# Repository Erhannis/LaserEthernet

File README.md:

Warning: I did not get it working, though I only spent like half an hour trying before I got distracted with something else.

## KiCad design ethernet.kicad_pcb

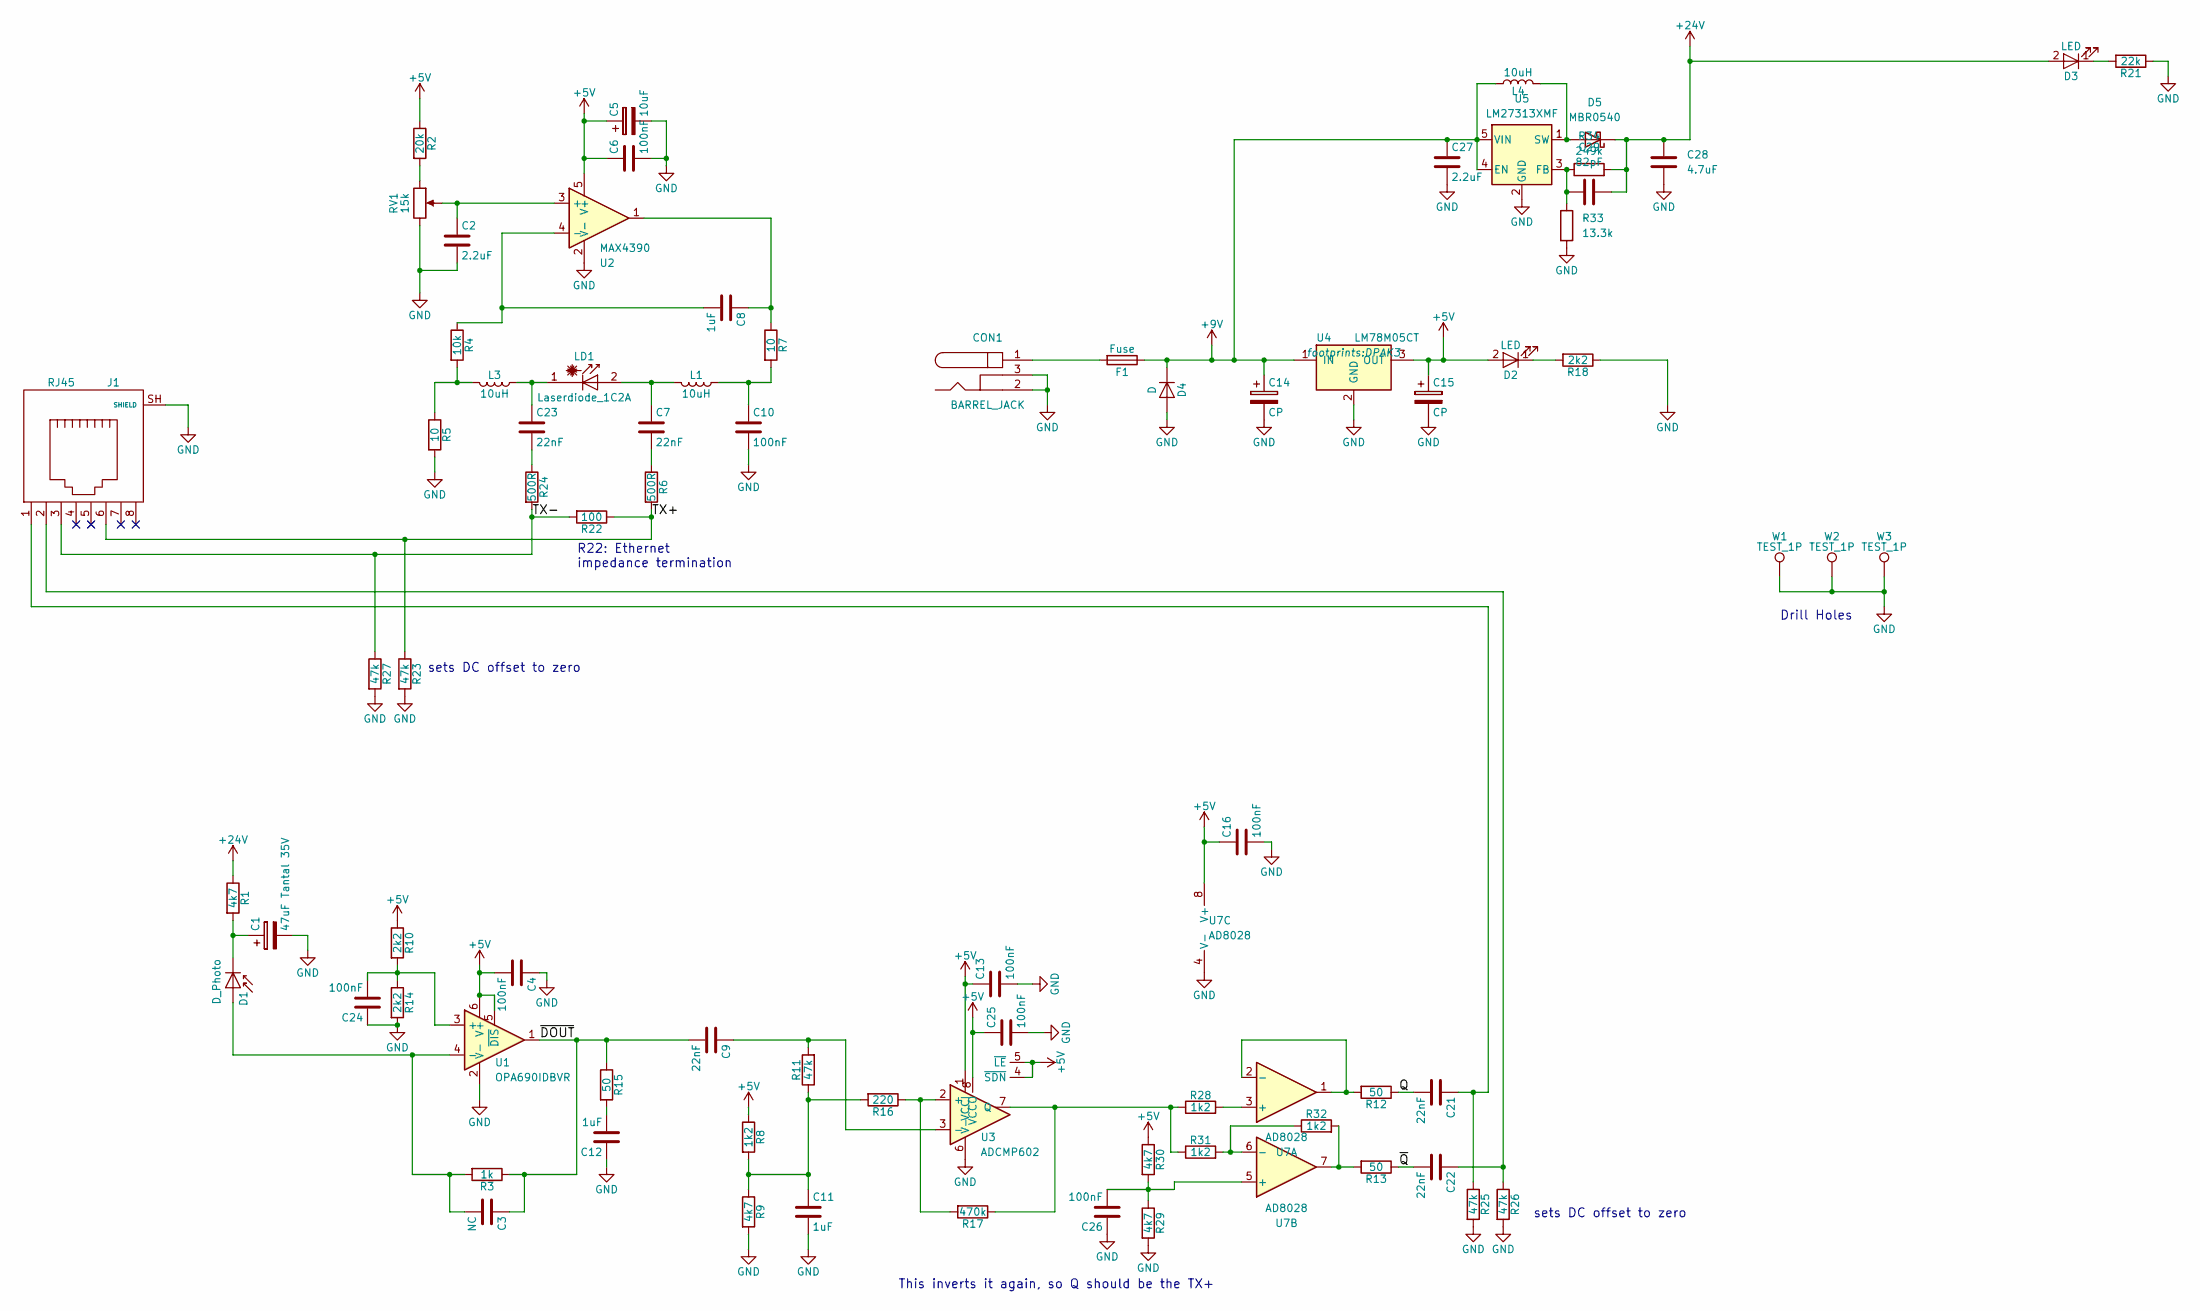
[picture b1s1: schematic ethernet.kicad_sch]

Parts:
C1: 47uF Tantal 35V; CP_Tantalum_Case-V_EIA-7343-20_Reflow; LCSC C600570
C2: 2.2uF; C_0603_HandSoldering; LCSC C913904
C3: NC; C_0603_HandSoldering
C4, C6, C10, C13, C24: 100nF; C_0603_HandSoldering; LCSC C30926
C5: 10uF; CP_Elec_4x5.8; LCSC C401709
C7, C9, C21, C22, C23: 22nF; C_0603_HandSoldering; LCSC C77571
C8, C11, C12: 1uF; C_0603_HandSoldering; LCSC C15849
C14, C15: CP; CP_Elec_4x5.8; LCSC C401709
C16, C25, C26: 100nF; C_0603_1608Metric_Pad1.08x0.95mm_HandSolder; LCSC C30926
C27: 2.2uF; C_0603_1608Metric; LCSC C913904
C28: 4.7uF; C_0603_1608Metric; LCSC C162274
C29: 82pF; C_0402_1005Metric; LCSC C526982
CON1: BARREL_JACK; LCSC C431533
D1: D_Photo; LED_D3.0mm_Horicontal_O2.54mm; LCSC C145493
D2: LED; D_0603_1608Metric; LCSC C72043
D3: LED; D_0603_1608Metric; LCSC C965808
D4: D; D_0603_1608Metric; LCSC C143772
D5: MBR0540; D_SOD-123
F1: Fuse; Fuseholder5x20_horiz_SemiClosed_Casing10x25mm; LCSC C58066
J1: RJ45; RJ45_Ninigi_GE; LCSC C3001538
L1, L3, L4: 10uH; L_1210_3225Metric; LCSC C250231
LD1: Laserdiode_1C2A; laserdiode_6mm
R1, R9: 4k7; R_0603_HandSoldering; LCSC C23162
R2: 20k; R_0603_HandSoldering; LCSC C4184
R3: 1k; R_0603_HandSoldering; LCSC C21190
R4: 10k; R_0603_HandSoldering; LCSC C25804
R5, R7: 10; R_0603_HandSoldering; LCSC C22859
R6, R24: 500R; R_0603_HandSoldering; LCSC C23065
R8: 1k2; R_0603_HandSoldering; LCSC C22765
R10, R14, R18: 2k2; R_0603_HandSoldering; LCSC C4190
R11, R23, R25, R26, R27: 47k; R_0603_HandSoldering; LCSC C25819
R12, R13, R15: 50; R_0603_HandSoldering; LCSC C23185
R16: 220; R_0603_HandSoldering; LCSC C22962
R17: 470k; R_0603_HandSoldering; LCSC C23178
R21: 22k; R_0603_HandSoldering; LCSC C31850
R22: 100; R_0603_HandSoldering; LCSC C22775
R28, R31, R32: 1k2; R_0603_1608Metric_Pad0.98x0.95mm_HandSolder; LCSC C22765
R29, R30: 4k7; R_0603_1608Metric_Pad0.98x0.95mm_HandSolder; LCSC C23162
R33: 13.3k; R_0402_1005Metric; LCSC C274352
R34: 249k; R_0402_1005Metric; LCSC C409682
RV1: 15k; TC33k; LCSC C128550
U1: OPA690IDBVR; SOT-23-6; LCSC C524799
U2: MAX4390; SOT-23-5; LCSC C652243
U3: ADCMP602; MSOP-8_3x3mm_P0.65mm; LCSC C207991
U4: LM78M05CT; DPAK3; LCSC C9070
U5: LM27313XMF; SOT-23-5
U7: AD8028; SOIC-8_3.9x4.9mm_P1.27mm; LCSC C652202
W1, W2, W3: TEST_1P; 3mm_drill

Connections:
+5V: C4.2, C5.1, C6.1, C13.1, C15.1, C16.1, C25.1, D2.2 (A), R2.1, R8.1, R10.1, R30.1, U1.5 (~DIS), U1.6 (V+), U2.5 (V+), U3.1 (VCCI), U3.4 (~SDN), U3.5 (~LE), U3.8 (VCCO), U4.3 (OUT), U7.8 (V+)
+9V: C14.1, C27.1, D4.1 (K), F1.1, L4.1, U4.1 (IN), U5.4 (EN), U5.5 (VIN)
+24V: C28.1, C29.2, D3.2 (A), D5.1 (K), R1.1, R34.2
/Q: C21.2, R12.1
/TX+: J1.6, R6.2, R22.1, R23.1
/TX-: J1.3, R22.2, R24.2, R27.1
/~DOUT: C3.1, C9.2, R3.1, R15.1, U1.1
/~Q: C22.2, R13.1
GND: C1.2, C2.2, C4.1, C5.2, C6.2, C10.2, C11.2, C12.1, C13.2, C14.2, C15.2, C16.2, C24.1, C25.2, C26.1, C27.2, C28.2, CON1.2, CON1.3, D4.2 (A), J1.SH (SHIELD), R5.2, R9.2, R14.2, R18.1, R21.1, R23.2, R25.2, R26.2, R27.2, R29.2, R33.2, RV1.3, U1.2 (V-), U2.2 (V-), U3.6 (V-), U4.2 (GND), U5.2 (GND), U7.4 (V-), W1.1, W2.1, W3.1
unnamed: C7.2, R6.1
unnamed: C8.1, R7.1, U2.1
unnamed: C10.1, L1.1, R7.2
unnamed: C11.1, R8.2, R9.1, R11.1, R16.2
unnamed: C12.2, R15.2
unnamed: C21.1, J1.1, R25.1
unnamed: C22.1, J1.2, R26.1
unnamed: C23.2, R24.1
unnamed: CON1.1, F1.2
unnamed: C3.2, D1.2 (A), R3.2, U1.4 (-)
unnamed: C1.1, D1.1 (K), R1.2
unnamed: D2.1 (K), R18.2
unnamed: D3.1 (K), R21.2
unnamed: D5.2 (A), L4.2, U5.1 (SW)
unnamed: L3.2, R4.2, R5.1
unnamed: C7.1, L1.2, LD1.2 (A)
unnamed: C23.1, L3.1, LD1.1 (K)
unnamed: R2.2, RV1.1
unnamed: R13.2, R32.2, U7.7
unnamed: C24.2, R10.2, R14.1, U1.3 (+)
unnamed: C2.1, RV1.2, U2.3 (+)
unnamed: C8.2, R4.1, U2.4 (-)
unnamed: R16.1, R17.2, U3.2 (+)
unnamed: C9.1, R11.2, U3.3 (-)
unnamed: R17.1, R28.1, R31.1, U3.7 (Q)
unnamed: C29.1, R33.1, R34.1, U5.3 (FB)
unnamed: R28.2, U7.3 (+)
unnamed: R12.2, U7.1, U7.2 (-)
unnamed: C26.2, R29.1, R30.2, U7.5 (+)
unnamed: R31.2, R32.1, U7.6 (-)

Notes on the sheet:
R22: Ethernet impedance termination
sets DC offset to zero
Drill Holes
This inverts it again, so Q should be the TX+

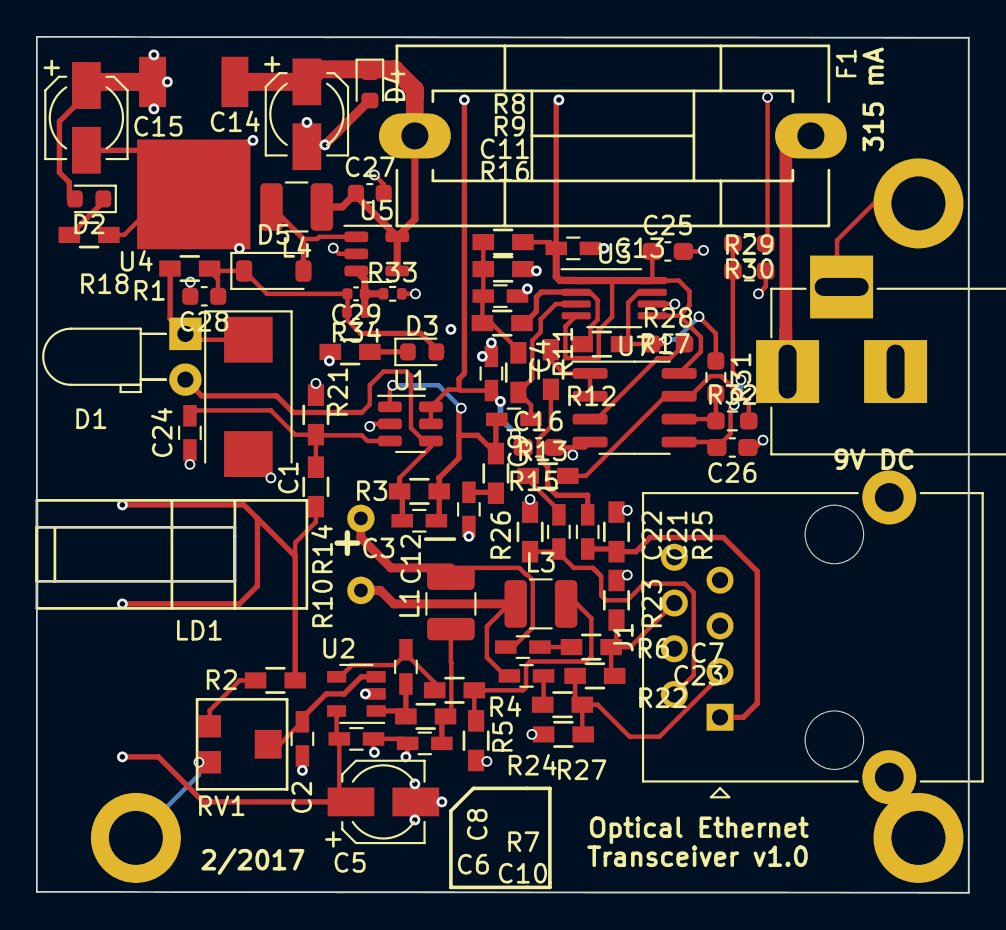
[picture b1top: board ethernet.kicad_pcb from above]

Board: 2 copper layers, 51.8 x 47.5 mm, 79 parts (0 on the bottom side), 39 nets.

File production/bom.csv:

Designator,Footprint,Quantity,Value,LCSC Part #
C1,CP_Tantalum_Case-V_EIA-7343-20_Reflow,1,47uF Tantal 35V,C600570
"C10, C13, C24, C4, C6",C_0603_HandSoldering,5,100nF,C30926
"C11, C12, C8",C_0603_HandSoldering,3,1uF,C15849
"C14, C15",CP_Elec_4x5.8,2,CP,C401709
"C16, C25, C26",0603,3,100nF,C30926
C2,C_0603_HandSoldering,1,2.2uF,C913904
"C21, C22, C23, C7, C9",C_0603_HandSoldering,5,22nF,C77571
C27,0603,1,2.2uF,C913904
C28,0603,1,4.7uF,C162274
C29,0402,1,82pF,C526982
C3,C_0603_HandSoldering,1,NC,
C5,CP_Elec_4x5.8,1,10uF,C401709
CON1,BARREL_JACK,1,BARREL_JACK,C431533
D1,LED_D3.0mm_Horicontal_O2.54mm,1,D_Photo,C145493
"D2, D3",R_0603_HandSoldering,2,LED,C72043
D4,C_0603_HandSoldering,1,D,C143772
D5,D_SOD-123,1,MBR0540,
F1,Fuseholder5x20_horiz_SemiClosed_Casing10x25mm,1,Fuse,C58066
J1,RJ45_Ninigi_GE,1,RJ45,C3001538
"L1, L3, L4",1210,3,10uH,C250231
LD1,laserdiode_6mm,1,Laserdiode_1C2A,
"R1, R9",R_0603_HandSoldering,2,4k7,C23162
"R10, R14, R18",R_0603_HandSoldering,3,2k2,C4190
"R11, R23, R25, R26, R27",R_0603_HandSoldering,5,47k,C25819
"R12, R13, R15",R_0603_HandSoldering,3,50,C23185
R16,R_0603_HandSoldering,1,220,C22962
R17,R_0603_HandSoldering,1,470k,C23178
R2,R_0603_HandSoldering,1,20k,C4184
R21,R_0603_HandSoldering,1,22k,C31850
R22,R_0603_HandSoldering,1,100,C22775
"R24, R6",R_0603_HandSoldering,2,500R,C23065
"R28, R31, R32",0603,3,1k2,C22765
"R29, R30",0603,2,4k7,C23162
R3,R_0603_HandSoldering,1,1k,C21190
R33,0402,1,13.3k,C274352
R34,0402,1,249k,C409682
R4,R_0603_HandSoldering,1,10k,C25804
"R5, R7",R_0603_HandSoldering,2,10,C22859
R8,R_0603_HandSoldering,1,1k2,C22765
RV1,TC33k,1,15k,C128550
U1,SOT-23-6,1,OPA690IDBVR,C524799
U2,SOT-23-5,1,MAX4390,C652243
U3,MSOP-8_3x3mm_P0.65mm,1,ADCMP602,C207991
U4,DPAK3,1,LM78M05CT,C9070
U5,SOT-23-5,1,LM27313XMF,
U7,SOIC-8_3.9x4.9mm_P1.27mm,1,AD8028,C652202
"W1, W2, W3",3mm_drill,3,TEST_1P,

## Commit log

2023-10-13 Clean repo; laser ethernet board from http://blog.svenbrauch.de/2017/02/19/homemade-10-mbits-laser-optical-ethernet-transceiver ; license CC-BY-SA-NC 4.0 ; plan is to add component IDs and send to jl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
2023-10-13 Kicad autoupgrade
2023-10-13 Selected resistors
2023-10-13 LEDs selected
2023-10-13 Electrolytic caps
2023-10-13 0603 caps
2023-10-13 Inductors (and saved from kicad so there are redundant positions saved)
2023-10-13 Tantalum cap and pot
2023-10-13 Two ICs and a diode
2023-10-13 OpAmp and power jack. Further components MAY require PCB changes.
2023-10-13 Picked photodiode and fuse holder. Warning: I don't know if this photodiode will work.
2023-10-13 PCB UPDATED. Specifically, the new ethernet socket needed rewiring.
2023-10-13 Generated JLCPCB production files. Currently still missing part selection for MAX4392, LT1713, and MIC2605. Laser diode omitted, for user to add, for aiming.
2023-10-13 Ok, I replaced the comparator and the op amps, with a system of parts I can get, which MAY work.
2023-10-13 Ok, well, that was horrible, and the snake pile of tangled traces I added to the board is even worse. I've flouted most of the things I've learned about avoiding crosstalk, etc. But at least everythi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
2023-10-13 Gah. Ok. Swapped out the 24V boost. Also fixed some mistakes.
2023-10-13 Sigh; missed a capacitor volt mismatch
2023-10-16 Some of the diode footprints were erroneously resistor/capacitor footprints, leading to ambiguous pcb markings
2024-09-23 Added readme with warning
